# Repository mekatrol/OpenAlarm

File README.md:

# OpenAlarm

An open source alarm system capable of integration with home automation systems. OpenAlarm is made up of hardware, firmware and software components to provide a secure and reliable alarm system.

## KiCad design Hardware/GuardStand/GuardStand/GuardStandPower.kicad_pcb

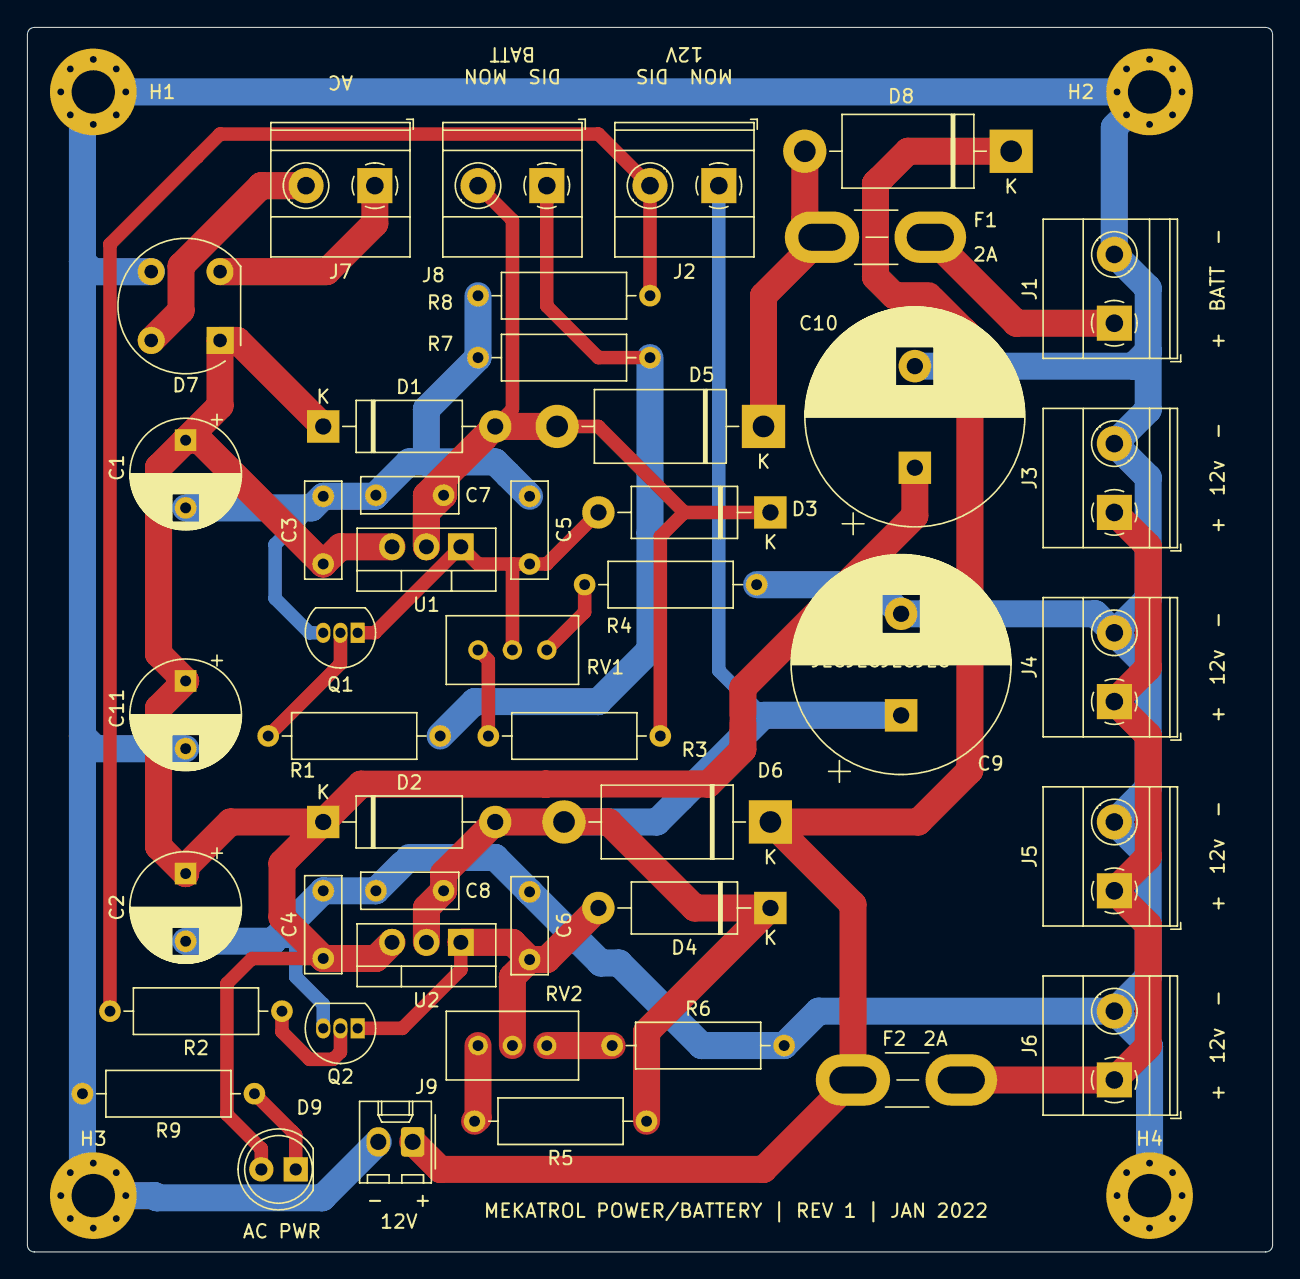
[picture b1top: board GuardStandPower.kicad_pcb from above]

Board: 2 copper layers, 91.9 x 90.4 mm, 50 parts (0 on the bottom side), 21 nets.

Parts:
C1, C2, C11: 100u; CP_Radial_D8.0mm_P5.00mm
C3, C4, C5, C6, C7, C8: 100n; C_Disc_D7.0mm_W2.5mm_P5.00mm
C9, C10: 2200u; CP_Radial_D16.0mm_P7.50mm
D1, D2, D3, D4: 1N4002; D_DO-15_P12.70mm_Horizontal
D5, D6, D8: 1N5400; D_DO-201AD_P15.24mm_Horizontal
D7: WO4; Diode_Bridge_Round_D9.8mm
D9: RED LED; LED_D5.0mm
F1, F2: 3A; Fuse_Blade_Mini_directSolder
H1, H2, H3, H4: GND; MountingHole_3.2mm_M3_Pad_Via
J1: BATT; TerminalBlock_Phoenix_MKDS-1,5-2-5.08_1x02_P5.08mm_Horizont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
J2, J8: DIS; TerminalBlock_Phoenix_MKDS-1,5-2-5.08_1x02_P5.08mm_Horizont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
J3, J4, J5, J6: 12V; TerminalBlock_Phoenix_MKDS-1,5-2-5.08_1x02_P5.08mm_Horizont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
J7: 15-18VAC; TerminalBlock_Phoenix_MKDS-1,5-2-5.08_1x02_P5.08mm_Horizont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
J9: 12v; Molex_KK-254_AE-6410-02A_1x02_P2.54mm_Vertical
Q1, Q2: BC549; TO-92_Inline
R1, R2, R9: 10k; R_Axial_DIN0309_L9.0mm_D3.2mm_P12.70mm_Horizontal
R3, R5: 240R; R_Axial_DIN0309_L9.0mm_D3.2mm_P12.70mm_Horizontal
R4: 2k32; R_Axial_DIN0309_L9.0mm_D3.2mm_P12.70mm_Horizontal
R6: 2k1; R_Axial_DIN0309_L9.0mm_D3.2mm_P12.70mm_Horizontal
R7, R8: 100k; R_Axial_DIN0309_L9.0mm_D3.2mm_P12.70mm_Horizontal
RV1, RV2: 500R; Potentiometer_Bourns_3296W_Vertical
U1, U2: LM317_TO-220; TO-220-3_Vertical

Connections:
12V_DIS: J2.2, R2.2, R8.2
12V_SUP: C8.1, C9.1, D2.2, D4.1, D6.2, J2.1, R5.1, U2.2
+15V: C1.1, C2.1, C3.1, C4.1, C10.1, C11.1, D1.1, D2.1, D7.1, D9.2, U1.3, U2.3
BATT_DIS: J8.1, R1.2, R7.2
BATT_SUP: C7.1, D1.2, D3.1, D5.2, J8.2, R3.1, U1.2
GND: C1.2, C2.2, C3.2, C4.2, C5.2, C6.2, C7.2, C8.2, C9.2, C10.2, C11.2, D7.3, H1.1, H2.1, H3.1, H4.1, J1.2, J3.2, J4.2, J5.2, J6.2, J9.2, Q1.3, Q2.3, R4.2, R6.2, R7.1, R8.1, R9.2
unnamed: C5.1, D3.2, Q1.1, RV1.2, U1.1
unnamed: C6.1, D4.2, Q2.1, RV2.2, U2.1
unnamed: D5.1, D8.2, F1.1
unnamed: D6.1, D8.1, F2.1, J9.1
unnamed: D7.2, J7.1
unnamed: D7.4, J7.2
unnamed: D9.1, R9.1
unnamed: F1.2, J1.1
unnamed: F2.2, J3.1, J4.1, J5.1, J6.1
unnamed: Q1.2, R1.1
unnamed: Q2.2, R2.1
unnamed: R3.2, RV1.3
unnamed: R4.1, RV1.1
unnamed: R5.2, RV2.3
unnamed: R6.1, RV2.1

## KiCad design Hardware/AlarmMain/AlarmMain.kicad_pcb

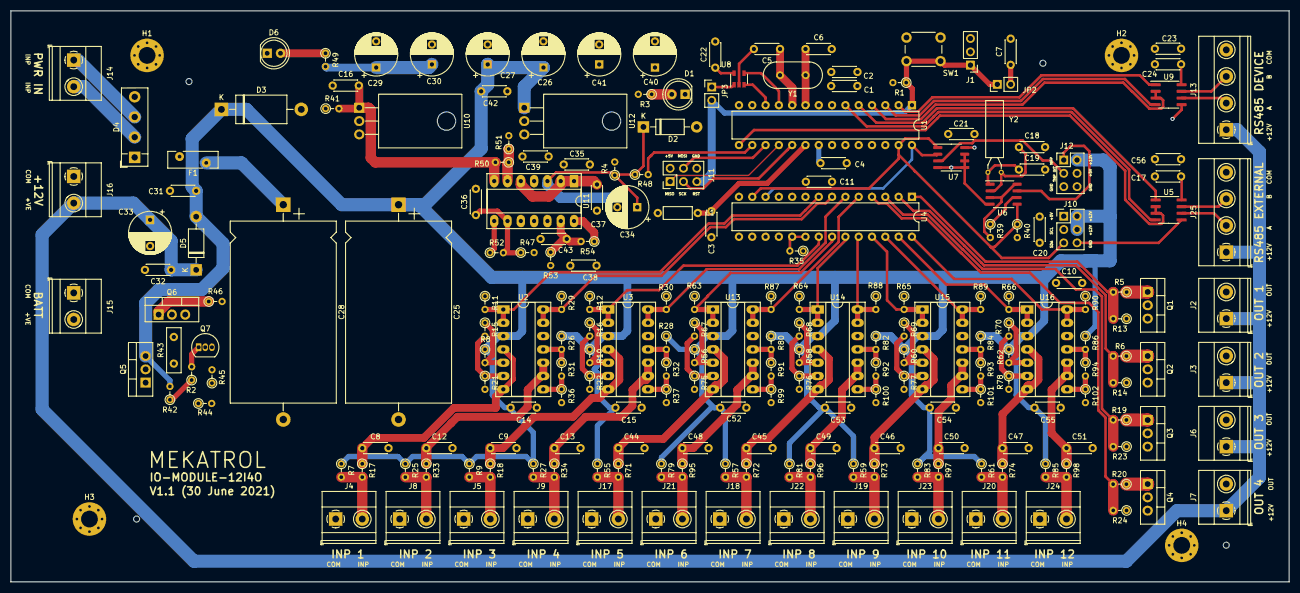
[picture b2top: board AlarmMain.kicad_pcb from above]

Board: 4 copper layers, 244.0 x 109.0 mm, 222 parts (0 on the bottom side), 130 nets.

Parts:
C1, C2, C3, C4, C7, C8, C9, C10, C11, C12, C13, C14, C15, C16, C17, C20, C21, C22, C23, C24, C31, C32, C35, C36, C37, C38, C39, C42, C43, C44, C45, C46, C47, C48, C49, C50, C51, C52, C53, C54, C55, C56: 100n; C_Disc_D4.3mm_W1.9mm_P5.00mm
C5, C6: 22p; C_Disc_D4.3mm_W1.9mm_P5.00mm
C18, C19: 10p; C_Disc_D4.3mm_W1.9mm_P5.00mm
C25, C28: 2200u; CP_Axial_L34.5mm_D20.0mm_P41.00mm_Horizontal
C26, C29, C40: 220u; CP_Radial_D8.0mm_P5.00mm
C27, C30, C41: 4.7u; CP_Radial_D8.0mm_P3.80mm
C33: 47u; CP_Radial_D8.0mm_P5.00mm
C34: 100u; CP_Radial_D8.0mm_P3.80mm
D1: LED; LED_D5.0mm
D2: 5V1; D_DO-41_SOD81_P10.16mm_Horizontal
D3: Schottky; D_DO-201_P15.24mm_Horizontal
D4: KBP210G; Diode_Bridge_Vishay_KBPM
D5: 1N5408RL; D_DO-41_SOD81_P10.16mm_Horizontal
D6: PWR; LED_D5.0mm
F1: 2A; Fuse_Bourns_MF-RHT200
H1, H2, H3, H4: GND; MountingHole_3.2mm_M3_Pad_Via
J1: debugWIRE; PinHeader_1x03_P2.54mm_Vertical
J2: OP1; TerminalBlock_Phoenix_MKDS-1,5-2-5.08_1x02_P5.08mm_Horizont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
J3: OP3; TerminalBlock_Phoenix_MKDS-1,5-2-5.08_1x02_P5.08mm_Horizont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
J4: DI9; TerminalBlock_Phoenix_MKDS-1,5-2-5.08_1x02_P5.08mm_Horizont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
J5: DI10; TerminalBlock_Phoenix_MKDS-1,5-2-5.08_1x02_P5.08mm_Horizont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
J6: OP2; TerminalBlock_Phoenix_MKDS-1,5-2-5.08_1x02_P5.08mm_Horizont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
J7: OP4; TerminalBlock_Phoenix_MKDS-1,5-2-5.08_1x02_P5.08mm_Horizont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
J8: DI11; TerminalBlock_Phoenix_MKDS-1,5-2-5.08_1x02_P5.08mm_Horizont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
J9: DI12; TerminalBlock_Phoenix_MKDS-1,5-2-5.08_1x02_P5.08mm_Horizont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
J10: I2C; PinHeader_2x03_P2.54mm_Vertical
J11: ICSP; PinHeader_2x03_P2.54mm_Vertical
J12: AUX; PinHeader_2x03_P2.54mm_Vertical
J13: RS485 1; TerminalBlock_Phoenix_MKDS-1,5-4-5.08_1x04_P5.08mm_Horizont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
J14: PWR; TerminalBlock_Phoenix_MKDS-1,5-2-5.08_1x02_P5.08mm_Horizont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
J15: BATT; TerminalBlock_Phoenix_MKDS-1,5-2-5.08_1x02_P5.08mm_Horizont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
J16: 12V; TerminalBlock_Phoenix_MKDS-1,5-2-5.08_1x02_P5.08mm_Horizont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
J17: DI1; TerminalBlock_Phoenix_MKDS-1,5-2-5.08_1x02_P5.08mm_Horizont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
J18: DI2; TerminalBlock_Phoenix_MKDS-1,5-2-5.08_1x02_P5.08mm_Horizont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
J19: DI3; TerminalBlock_Phoenix_MKDS-1,5-2-5.08_1x02_P5.08mm_Horizont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
J20: DI4; TerminalBlock_Phoenix_MKDS-1,5-2-5.08_1x02_P5.08mm_Horizont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
J21: DI5; TerminalBlock_Phoenix_MKDS-1,5-2-5.08_1x02_P5.08mm_Horizont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
J22: DI6; TerminalBlock_Phoenix_MKDS-1,5-2-5.08_1x02_P5.08mm_Horizont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
J23: DI7; TerminalBlock_Phoenix_MKDS-1,5-2-5.08_1x02_P5.08mm_Horizont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
J24: DI8; TerminalBlock_Phoenix_MKDS-1,5-2-5.08_1x02_P5.08mm_Horizont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
J25: RS485 2; TerminalBlock_Phoenix_MKDS-1,5-4-5.08_1x04_P5.08mm_Horizont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
JP2, JP3: NC; PinHeader_1x02_P2.54mm_Vertical
L1: 10u; L_Axial_L5.3mm_D2.2mm_P7.62mm_Horizontal_Vishay_IM-1
Q1, Q2, Q3, Q4: STP40NF03L; TO-220-3_Vertical
Q5: IRF9540N; TO-220-3_Vertical
Q6: IRF540N; TO-220-3_Vertical
Q7: BC337; TO-92_Inline
R1, R4, R13, R14, R23, R24, R35, R42, R44: 100K; R_Axial_DIN0204_L3.6mm_D1.6mm_P2.54mm_Vertical
R2, R39, R40, R51: 4K7; R_Axial_DIN0204_L3.6mm_D1.6mm_P2.54mm_Vertical
R3, R17, R18, R33, R34, R49, R71, R72, R73, R74, R95, R96, R97, R98: 330R; R_Axial_DIN0204_L3.6mm_D1.6mm_P2.54mm_Vertical
R5, R6, R19, R20: 100R; R_Axial_DIN0204_L3.6mm_D1.6mm_P2.54mm_Vertical
R7, R9, R25, R27, R55, R57, R59, R61, R79, R81, R83, R85: 2.2K; R_Axial_DIN0204_L3.6mm_D1.6mm_P2.54mm_Vertical
R8, R10, R11, R12, R15, R16, R21, R22, R26, R28, R29, R30, R31, R32, R36, R37, R46, R47, R50, R53, R56, R58, R60, R62, R63, R64, R65, R66, R67, R68, R69, R70, R75, R76, R77, R78, R80, R82, R84, R86, R87, R88, R89, R90, R91, R92, R93, R94, R99, R100, R101, R102: 10K; R_Axial_DIN0204_L3.6mm_D1.6mm_P2.54mm_Vertical
R41: 220R; R_Axial_DIN0204_L3.6mm_D1.6mm_P2.54mm_Vertical
R43: 25R; R_Box_L8.4mm_W2.5mm_P5.08mm
R45: 200R; R_Axial_DIN0204_L3.6mm_D1.6mm_P2.54mm_Vertical
R48: 1K; R_Axial_DIN0204_L3.6mm_D1.6mm_P2.54mm_Vertical
R52, R54: 1.8K; R_Axial_DIN0204_L3.6mm_D1.6mm_P2.54mm_Vertical
SW1: RESET; SW_PUSH_6mm_H4.3mm
U1: ATmega328P-PU; DIP-28_W7.62mm
U2, U3, U13, U14, U15, U16: LM339; DIP-14_W7.62mm_Socket_LongPads
U4: MCP23017_SP; DIP-28_W7.62mm
U5, U9: MAX483E; SOIC-8_3.9x4.9mm_P1.27mm
U6: MCP7940N-xSN; SO-8_3.9x4.9mm_P1.27mm
U7: STTS75; SO-8_3.9x4.9mm_P1.27mm
U8: STWD100; SOT-23-5
U10: LM317_TO-220; TO-220-3_Horizontal_TabDown
U11: LM324; DIP-14_W7.62mm_Socket_LongPads
U12: 7805; TO-220-3_Horizontal_TabDown
Y1: 20Mhz; Crystal_HC49-U_Vertical
Y2: 32.768k; Crystal_AT310_D3.0mm_L10.0mm_Horizontal

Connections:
+5V: C1.1, C2.1, C10.1, C11.1, C17.1, C20.1, C21.1, C22.1, C23.1, C24.1, C39.1, C40.1, C41.1, C56.1, J1.2, J10.1, J11.2, J12.4, L1.1, R1.2, R3.2, R11.1, R12.1, R29.1, R30.1, R35.1, R39.2, R40.2, R63.1, R64.1, R65.1, R66.1, R87.1, R88.1, R89.1, R90.1, U1.7, U4.9, U5.8, U6.3, U6.8, U7.8, U8.5, U9.8, U12.3
+12V: C32.1, C33.1, D5.1, J2.1, J3.1, J6.1, J7.1, J13.1, J16.2, J25.1
AC2: D4.3, J14.1
DI1: R63.2, U4.22, U13.1, U13.2
DI2: R64.2, U4.23, U14.1, U14.2
DI3: R65.2, U4.25, U15.1, U15.2
DI4: R66.2, U4.27, U16.1, U16.2
DI5: R87.2, U4.5, U13.13, U13.14
DI6: R88.2, U4.24, U14.13, U14.14
DI7: R89.2, U4.26, U15.13, U15.14
DI8: R90.2, U4.28, U16.13, U16.14
DI9: R11.2, U2.1, U2.2, U4.8
DI10: R12.2, U3.1, U3.2, U4.21
DI11: R29.2, U2.13, U2.14, U4.7
DI12: R30.2, U3.13, U3.14, U4.6
DO1: R20.2, R24.2, U4.4
DO2: R19.2, R23.2, U4.3
DO3: R6.2, R14.2, U4.2
DO4: R5.2, R13.2, U4.1
GND: C1.2, C2.2, C3.2, C4.2, C5.2, C6.2, C7.2, C8.2, C9.2, C10.2, C11.2, C12.2, C13.2, C14.2, C15.2, C17.2, C18.2, C19.2, C20.2, C21.2, C22.2, C23.2, C24.2, C25.2, C26.2, C27.2, C28.2, C29.2, C30.2, C31.2, C32.2, C33.2, C34.2, C35.2, C36.2, C37.2, C38.2, C39.2, C40.2, C41.2, C42.2, C43.2, C44.2, C45.2, C46.2, C47.2, C48.2, C49.2, C50.2, C51.2, C52.2, C53.2, C54.2, C55.2, C56.2, D2.2, D4.4, D6.1, H1.1, H2.1, H3.1, H4.1, J1.3, J4.1, J5.1, J8.1, J9.1, J10.6, J11.6, J12.5, J12.6, J13.4, J15.1, J16.1, J17.1, J18.1, J19.1, J20.1, J21.1, J22.1, J23.1, J24.1, J25.4, Q1.3, Q2.3, Q3.3, Q4.3, Q6.3, Q7.3, R13.1, R14.1, R21.2, R22.2, R23.1, R24.1, R36.2, R37.2, R44.1, R51.2, R75.2, R76.2, R77.2, R78.2, R99.2, R100.2, R101.2, R102.2, SW1.2, U1.8, U1.22, U2.12, U3.12, U4.10, U4.15, U4.16, U4.17, U5.5, U6.4, U7.4, U7.5, U7.6, U7.7, U8.2, U9.5, U11.10, U11.11, U11.12, U12.2, U13.12, U14.12, U15.12, U16.12
IO_INT: R35.2, U1.13, U4.19, U4.20
LED1: D1.1, U1.14
MFP: J12.1, U6.7
MISO: J11.1, U1.18
MOSI: J11.4, U1.17
unnamed: C3.1, L1.2, U1.20
unnamed: C4.1, U1.21
unnamed: C5.1, U1.10, Y1.2
unnamed: C6.1, U1.9, Y1.1
unnamed: C7.1, JP2.2
unnamed: C8.1, R17.1, U2.4, U2.7
unnamed: C9.1, R18.1, U3.4, U3.7
unnamed: C12.1, R33.1, U2.9, U2.10
unnamed: C13.1, R34.1, U3.9, U3.10
unnamed: C16.1, D3.2, R41.1, U10.2
unnamed: C18.1, U6.2, Y2.1
unnamed: C19.1, U6.1, Y2.2
unnamed: C34.1, D2.1, R4.1, R48.1, U11.3
unnamed: C36.1, R47.1, R52.2, U11.9
unnamed: C37.1, U11.1, U11.2, U11.5
unnamed: C43.1, R53.1, R54.2, U11.13
unnamed: C44.1, R71.1, U13.4, U13.7
unnamed: C45.1, R72.1, U14.4, U14.7
unnamed: C46.1, R73.1, U15.4, U15.7
unnamed: C47.1, R74.1, U16.4, U16.7
unnamed: C48.1, R95.1, U13.9, U13.10
unnamed: C49.1, R96.1, U14.9, U14.10
unnamed: C50.1, R97.1, U15.9, U15.10
unnamed: C51.1, R98.1, U16.9, U16.10
unnamed: D1.2, R3.1
unnamed: D4.1, F1.2
unnamed: D4.2, J14.2
unnamed: D6.2, R49.1
unnamed: J2.2, Q1.2
unnamed: J3.2, Q2.2
unnamed: J4.2, R7.2, R17.2
unnamed: J5.2, R9.2, R18.2
unnamed: J6.2, Q3.2
unnamed: J7.2, Q4.2
unnamed: J8.2, R25.2, R33.2
unnamed: J9.2, R27.2, R34.2
unnamed: J13.2, U9.6
unnamed: J13.3, U9.7
unnamed: J17.2, R55.2, R71.2
unnamed: J18.2, R57.2, R72.2
unnamed: J19.2, R59.2, R73.2
unnamed: J20.2, R61.2, R74.2
unnamed: J21.2, R79.2, R95.2
unnamed: J22.2, R81.2, R96.2
unnamed: J23.2, R83.2, R97.2
unnamed: J24.2, R85.2, R98.2
unnamed: J25.2, U5.6
unnamed: J25.3, U5.7
unnamed: JP3.1, U8.1
unnamed: Q1.1, R5.1
unnamed: Q2.1, R6.1
unnamed: Q3.1, R19.1
unnamed: Q4.1, R20.1
unnamed: Q5.1, R2.1, R42.1
unnamed: Q6.1, R46.1
unnamed: Q6.2, R43.2
unnamed: Q7.1, R2.2
unnamed: Q7.2, R44.2, R45.2
unnamed: R10.2, R16.1, U3.5
unnamed: R8.2, R15.1, U2.5
unnamed: R15.2, R21.1, U2.6
unnamed: R16.2, R22.1, U3.6
unnamed: R26.2, R31.1, U2.11
unnamed: R28.2, R32.1, U3.11
unnamed: R31.2, R36.1, U2.8
unnamed: R32.2, R37.1, U3.8
unnamed: R50.1, R51.1, U11.6
unnamed: R56.2, R67.1, U13.5
unnamed: R58.2, R68.1, U14.5
unnamed: R60.2, R69.1, U15.5
unnamed: R62.2, R70.1, U16.5
unnamed: R67.2, R75.1, U13.6
unnamed: R68.2, R76.1, U14.6
unnamed: R69.2, R77.1, U15.6
unnamed: R70.2, R78.1, U16.6
unnamed: R80.2, R91.1, U13.11
unnamed: R82.2, R92.1, U14.11
unnamed: R84.2, R93.1, U15.11
unnamed: R86.2, R94.1, U16.11
unnamed: R91.2, R99.1, U13.8
unnamed: R92.2, R100.1, U14.8
unnamed: R93.2, R101.1, U15.8
unnamed: R94.2, R102.1, U16.8
PD5: U1.11, U8.4
PD6: U1.12, U8.3
RESET: J1.1, J11.5, JP2.1, JP3.2, R1.1, SW1.1, U1.1, U4.18
RTS: U1.4, U9.2, U9.3
RTS_2: U1.15, U5.2, U5.3
RXD: U1.2, U9.1
RXD_2: U1.5, U5.1
SCK: J11.3, U1.19
SCL: J10.3, R39.1, U1.28, U4.12, U6.6, U7.2
SDA: J10.5, R40.1, U1.27, U4.13, U6.5, U7.1
TEMP_INT: J12.3, U7.3
TXD: U1.3, U9.4
TXD_2: U1.6, U5.4
VBAT: C38.1, J15.2, Q5.2, R43.1, R53.2
VBAT_ADJ: C16.2, R41.2, R50.2, U10.1, U11.7
VBAT_DIS: R45.1, U1.24
VBAT_MON: R54.1, U1.26, U11.14
VBAT_PWM: R48.2, U1.16
VBAT_SUP: C14.1, C15.1, C25.1, C26.1, C27.1, C31.1, C42.1, C52.1, C53.1, C54.1, C55.1, D3.1, D5.2, J10.2, J10.4, J12.2, Q5.3, R7.1, R8.1, R9.1, R10.1, R25.1, R26.1, R27.1, R28.1, R42.2, R55.1, R56.1, R57.1, R58.1, R59.1, R60.1, R61.1, R62.1, R79.1, R80.1, R81.1, R82.1, R83.1, R84.1, R85.1, R86.1, U2.3, U3.3, U12.1, U13.3, U14.3, U15.3, U16.3
VBAT_TEST: R46.2, U1.23
VIN: C28.1, C29.1, C30.1, C35.1, F1.1, R4.2, R47.2, R49.2, U10.3, U11.4
VPWR_MON: R52.1, U1.25, U11.8

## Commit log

2021-04-24 Update README.md
    Added initial brief description
2021-04-24 Update README.md
    Update to README
2021-05-20 Progressive check in (firmware/hardware)
2021-05-21 PCB progressive updates
2021-05-21 Furst python layout scripts
2021-05-21 Progressive layout
2021-05-21 Input connector order change
2021-05-21 Completed tracks first pass
2021-05-22 Rework to 4 layers
2021-05-28 Moved files
2021-05-28 Renamed to proto
2021-06-02 Fixes to PCB silkscreen
2021-06-02 Rev 1.1 (Power boot zener)
2022-01-30 Remove unused design
2022-01-30 Updated calcs
2022-01-30 Power board
2022-01-31 Design updates
